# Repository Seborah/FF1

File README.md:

# FF1
The first ForgFactory keyboard

A fully custom USB-C numpad made with an ATMEGA32U4 and QMK.

# Kicanvas
[Daughter Board](https://kicanvas.org/?github=https%3A%2F%2Fgithub.com%2FSeborah%2FFF1%2Ftree%2Fmain%2Fdaughter%2520board)
[Button Board](https://kicanvas.org/?github=https%3A%2F%2Fgithub.com%2FSeborah%2FFF1%2Ftree%2Fmain%2Fbutton%2520pcb)

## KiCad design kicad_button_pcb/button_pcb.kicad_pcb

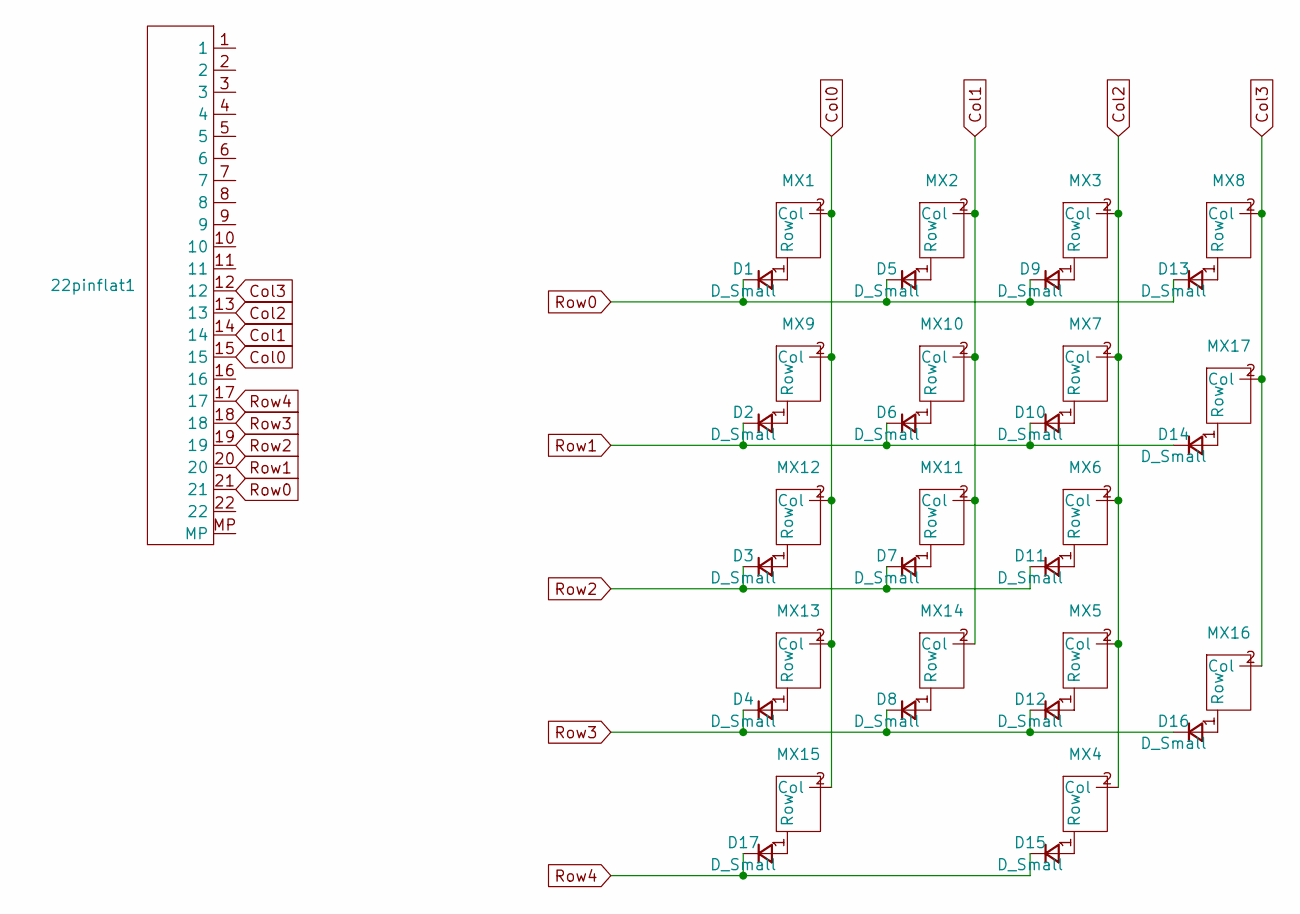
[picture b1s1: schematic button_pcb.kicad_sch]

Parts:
22pinflat1: Hirose_FH12-22S-0.5SH_1x22-1MP_P0.50mm_Horizontal
D1, D2, D3, D4, D5, D6, D7, D8, D9, D10, D11, D12, D13, D14, D15, D16, D17: D_Small; D_SOD-123
MX1, MX2, MX3, MX4, MX5, MX6, MX7, MX8, MX9, MX10, MX11, MX12, MX13, MX14: MX-Hotswap-1U
MX15: MX-Hotswap-2U-ReversedStabilizers
MX16, MX17: MX-Hotswap-2U-Vertical

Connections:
Col0: 22pinflat1.15, MX1.2 (Col), MX9.2 (Col), MX12.2 (Col), MX13.2 (Col), MX15.2 (Col)
Col1: 22pinflat1.14, MX2.2 (Col), MX10.2 (Col), MX11.2 (Col), MX14.2 (Col)
Col2: 22pinflat1.13, MX3.2 (Col), MX4.2 (Col), MX5.2 (Col), MX6.2 (Col), MX7.2 (Col)
Col3: 22pinflat1.12, MX8.2 (Col), MX16.2 (Col), MX17.2 (Col)
unnamed: D1.2 (A), MX1.1 (Row)
unnamed: D2.2 (A), MX9.1 (Row)
unnamed: D3.2 (A), MX12.1 (Row)
unnamed: D4.2 (A), MX13.1 (Row)
unnamed: D5.2 (A), MX2.1 (Row)
unnamed: D6.2 (A), MX10.1 (Row)
unnamed: D7.2 (A), MX11.1 (Row)
unnamed: D8.2 (A), MX14.1 (Row)
unnamed: D9.2 (A), MX3.1 (Row)
unnamed: D10.2 (A), MX7.1 (Row)
unnamed: D11.2 (A), MX6.1 (Row)
unnamed: D12.2 (A), MX5.1 (Row)
unnamed: D13.2 (A), MX8.1 (Row)
unnamed: D14.2 (A), MX17.1 (Row)
unnamed: D15.2 (A), MX4.1 (Row)
unnamed: D16.2 (A), MX16.1 (Row)
unnamed: D17.2 (A), MX15.1 (Row)
Row0: 22pinflat1.21, D1.1 (K), D5.1 (K), D9.1 (K), D13.1 (K)
Row1: 22pinflat1.20, D2.1 (K), D6.1 (K), D10.1 (K), D14.1 (K)
Row2: 22pinflat1.19, D3.1 (K), D7.1 (K), D11.1 (K)
Row3: 22pinflat1.18, D4.1 (K), D8.1 (K), D12.1 (K), D16.1 (K)
Row4: 22pinflat1.17, D15.1 (K), D17.1 (K)

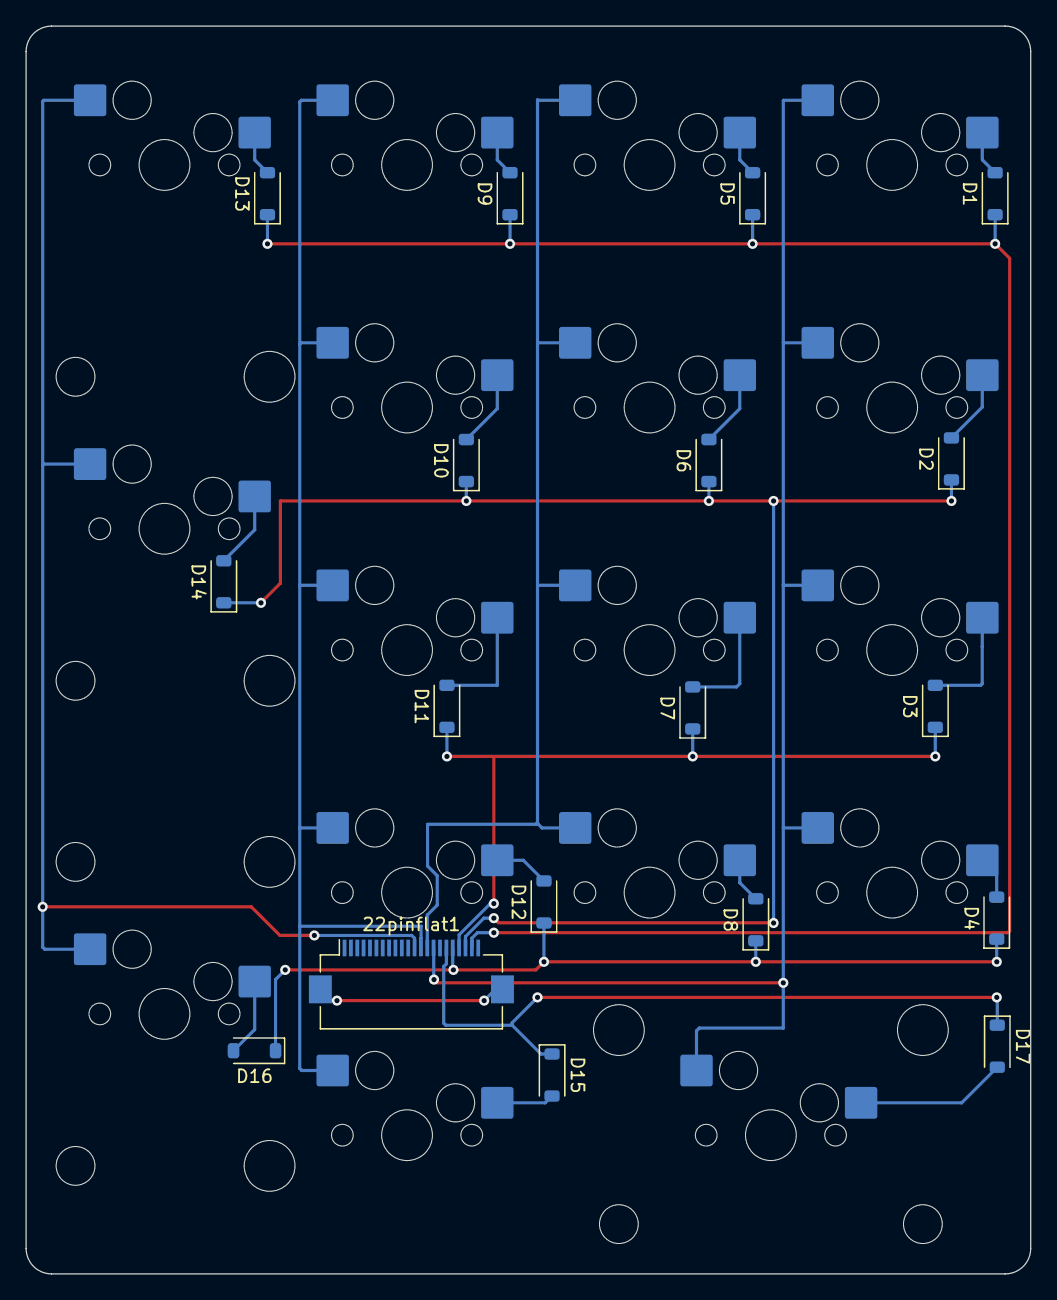
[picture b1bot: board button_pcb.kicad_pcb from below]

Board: 2 copper layers, 78.9 x 98.0 mm, 35 parts (18 on the bottom side), 26 nets.

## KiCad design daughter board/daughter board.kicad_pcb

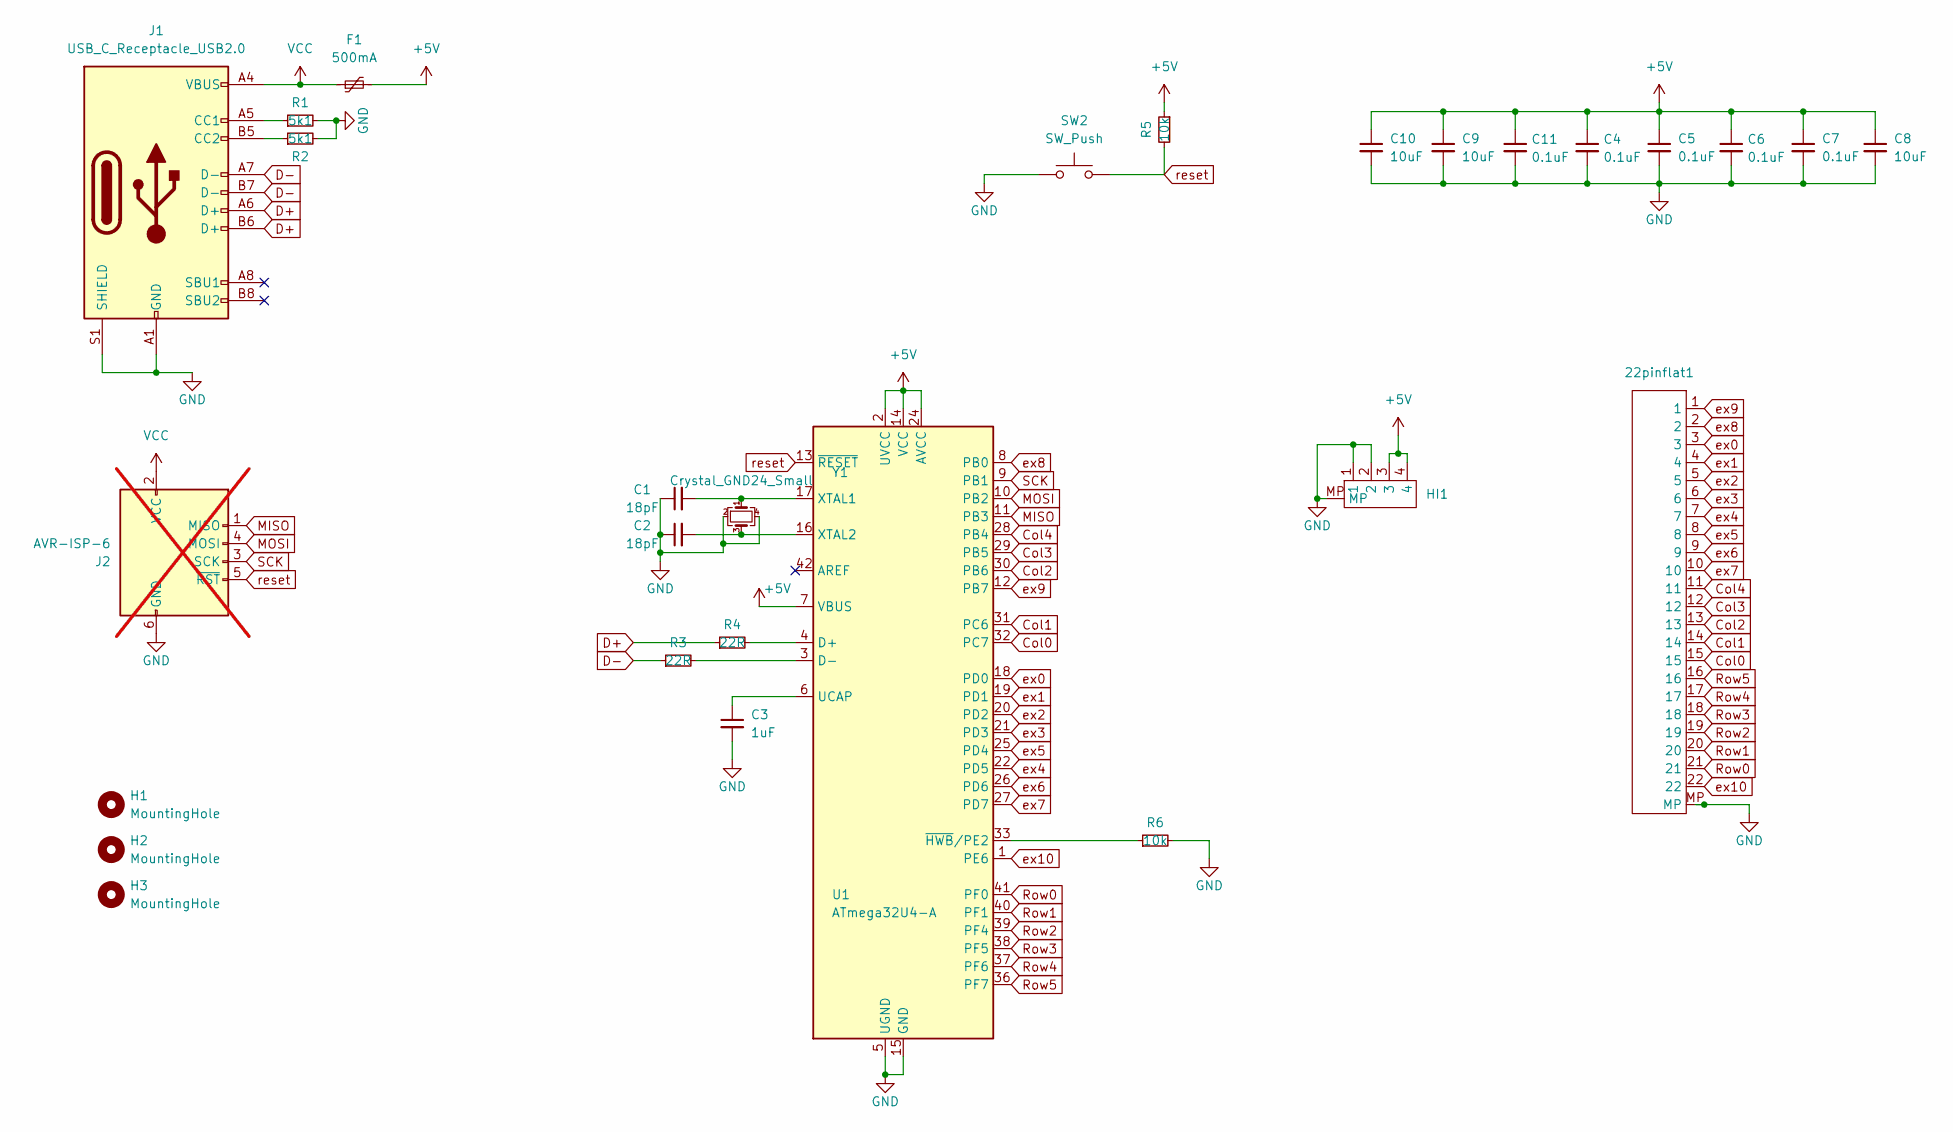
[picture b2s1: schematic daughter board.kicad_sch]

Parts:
22pinflat1: TE_2-1734839-2_1x22-1MP_P0.5mm_Horizontal
C1, C2: 18pF; C_0805_2012Metric
C3: 1uF; C_0805_2012Metric
C4, C5, C6, C7, C11: 0.1uF; C_0805_2012Metric
C8, C9, C10: 10uF; C_0805_2012Metric
F1: 500mA; Fuse_1206_3216Metric
H1, H2, H3: MountingHole; MountingHole_2.5mm_Pad
HI1: Hirose_DF52-4S-0.8H_1x04-1MP_P0.80mm_Horizontal
J1: USB_C_Receptacle_USB2.0; USB_C_Receptacle_HCTL_HC-TYPE-C-16P-01A
J2: AVR-ISP-6; IDC-Header_2x03_P2.54mm_Vertical; not fitted
R1, R2: 5k1; R_0805_2012Metric
R3, R4: 22R; R_0805_2012Metric
R5, R6: 10k; R_0805_2012Metric
SW2: SW_Push; SW_SPST_SKQG_WithStem
U1: ATmega32U4-A; TQFP-44_10x10mm_P0.8mm
Y1: Crystal_GND24_Small; Crystal_SMD_3225-4Pin_3.2x2.5mm

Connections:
+5V: C4.1, C5.1, C6.1, C7.1, C8.1, C9.1, C10.1, C11.1, F1.2, HI1.3, HI1.4, R5.1, U1.2 (UVCC), U1.7 (VBUS), U1.14 (VCC), U1.24 (AVCC), U1.34 (VCC), U1.44 (AVCC)
Col0: 22pinflat1.15, U1.32 (PC7)
Col1: 22pinflat1.14, U1.31 (PC6)
Col2: 22pinflat1.13, U1.30 (PB6)
Col3: 22pinflat1.12, U1.29 (PB5)
Col4: 22pinflat1.11, U1.28 (PB4)
D+: J1.A6 (D+), J1.B6 (D+), R4.1
D-: J1.A7 (D-), J1.B7 (D-), R3.1
GND: 22pinflat1.MP, C1.1, C2.1, C3.2, C4.2, C5.2, C6.2, C7.2, C8.2, C9.2, C10.2, C11.2, HI1.1, HI1.2, HI1.MP, J1.A1 (GND), J1.A12 (GND), J1.B1 (GND), J1.B12 (GND), J1.S1 (SHIELD), J2.6 (GND), R1.2, R2.2, R6.2, SW2.1, U1.5 (UGND), U1.15 (GND), U1.23 (GND), U1.35 (GND), U1.43 (GND), Y1.2, Y1.4
MISO: J2.1 (MISO), U1.11 (PB3)
MOSI: J2.4 (MOSI), U1.10 (PB2)
unnamed: J1.A5 (CC1), R1.1
unnamed: J1.B5 (CC2), R2.1
unnamed: R4.2, U1.4 (D+)
unnamed: R3.2, U1.3 (D-)
unnamed: C3.1, U1.6 (UCAP)
unnamed: C1.2, U1.17 (XTAL1), Y1.1
unnamed: C2.2, U1.16 (XTAL2), Y1.3
unnamed: R6.1, U1.33 (~HWB/PE2)
Row0: 22pinflat1.21, U1.41 (PF0)
Row1: 22pinflat1.20, U1.40 (PF1)
Row2: 22pinflat1.19, U1.39 (PF4)
Row3: 22pinflat1.18, U1.38 (PF5)
Row4: 22pinflat1.17, U1.37 (PF6)
Row5: 22pinflat1.16, U1.36 (PF7)
SCK: J2.3 (SCK), U1.9 (PB1)
VCC: F1.1, J1.A4 (VBUS), J1.A9 (VBUS), J1.B4 (VBUS), J1.B9 (VBUS), J2.2 (VCC)
ex0: 22pinflat1.3, U1.18 (PD0)
ex1: 22pinflat1.4, U1.19 (PD1)
ex2: 22pinflat1.5, U1.20 (PD2)
ex3: 22pinflat1.6, U1.21 (PD3)
ex4: 22pinflat1.7, U1.22 (PD5)
ex5: 22pinflat1.8, U1.25 (PD4)
ex6: 22pinflat1.9, U1.26 (PD6)
ex7: 22pinflat1.10, U1.27 (PD7)
ex8: 22pinflat1.2, U1.8 (PB0)
ex9: 22pinflat1.1, U1.12 (PB7)
ex10: 22pinflat1.22, U1.1 (PE6)
reset: J2.5 (~RST), R5.2, SW2.2, U1.13 (~RESET)

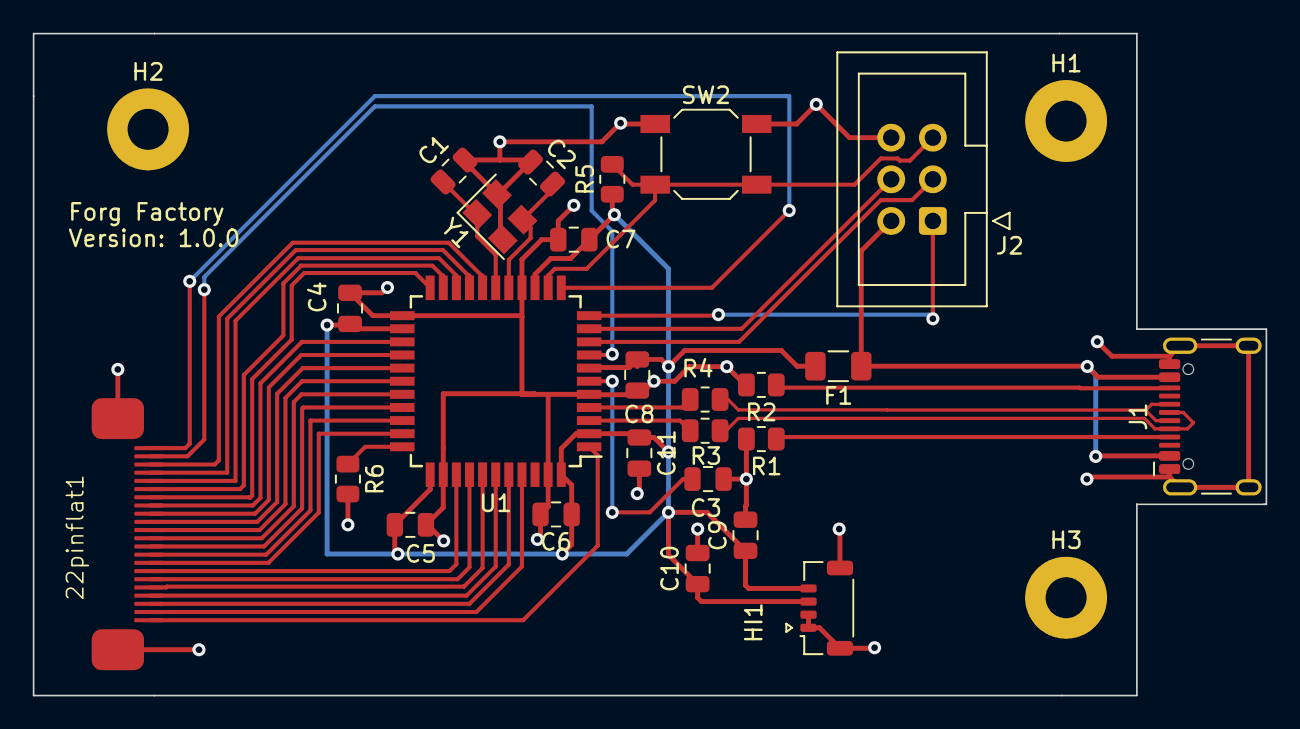
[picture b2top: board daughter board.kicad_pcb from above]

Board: 2 copper layers, 75.2 x 40.4 mm, 28 parts (0 on the bottom side), 39 nets.

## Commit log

2024-12-19 add images
2024-12-19 meow meow
2024-12-19 readme
2025-01-05 rename directories
